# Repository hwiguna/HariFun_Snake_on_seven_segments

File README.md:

# HariFun_Snake_on_seven_segments

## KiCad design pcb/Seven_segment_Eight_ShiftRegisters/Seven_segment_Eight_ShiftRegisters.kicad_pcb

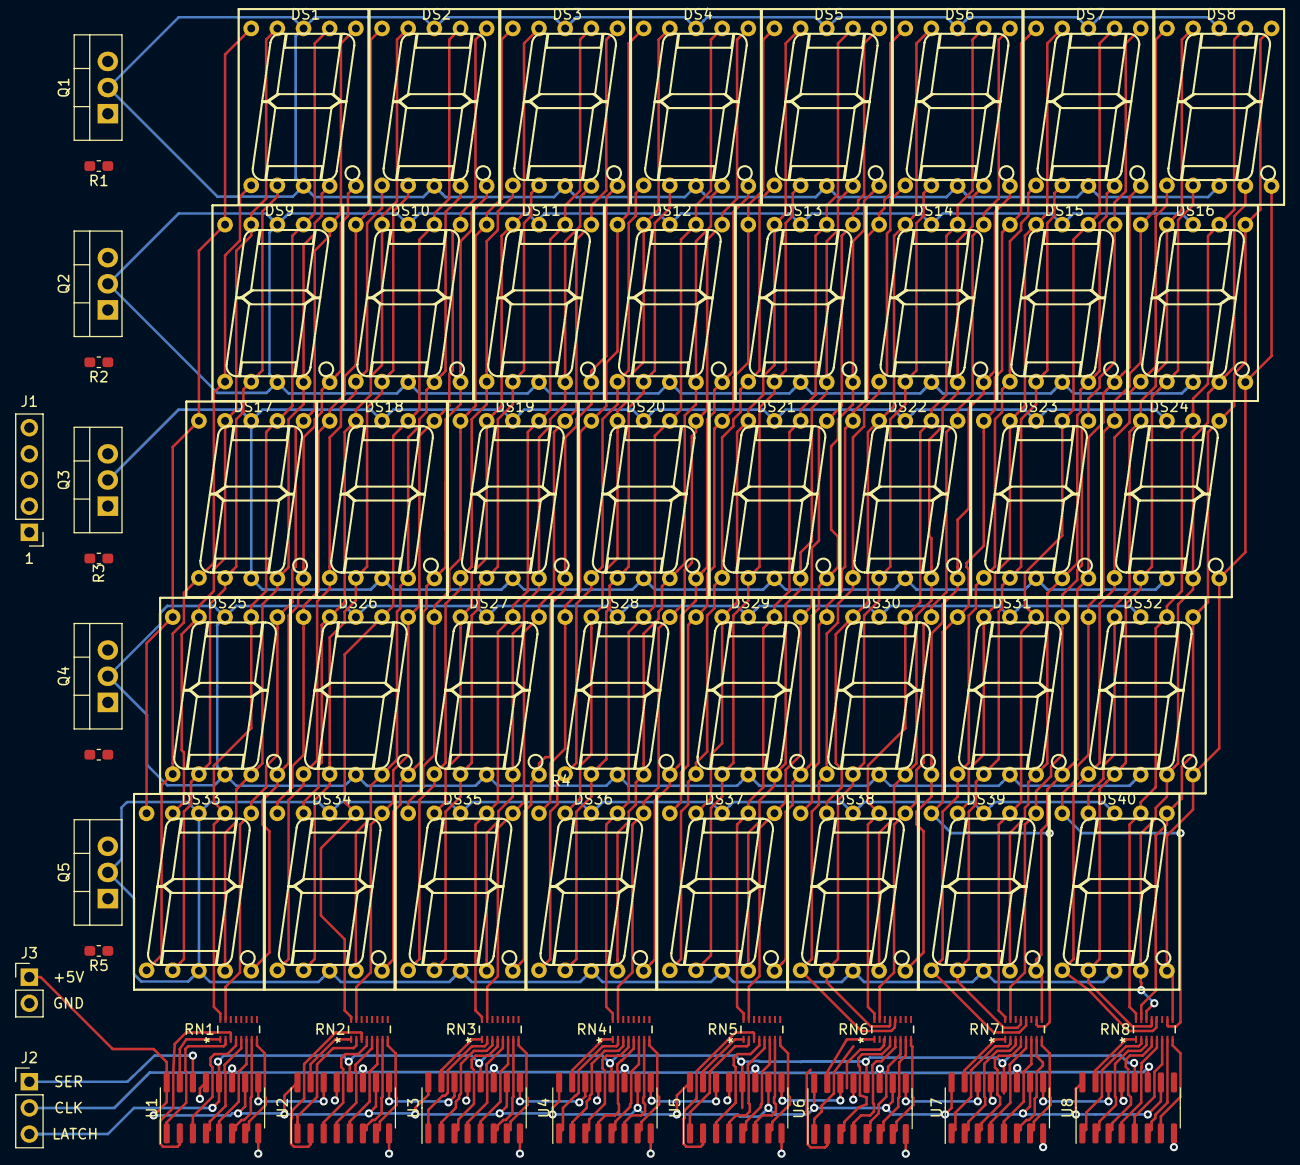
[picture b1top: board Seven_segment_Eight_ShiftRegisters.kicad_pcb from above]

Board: 2 copper layers, 69 parts (0 on the bottom side), 155 nets.

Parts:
DS1, DS2, DS3, DS4, DS5, DS6, DS7, DS8, DS9, DS10, DS11, DS12, DS13, DS14, DS15, DS16, DS17, DS18, DS19, DS20, DS21, DS22, DS23, DS24, DS25, DS26, DS27, DS28, DS29, DS30, DS31, DS32, DS33, DS34, DS35, DS36, DS37, DS38, DS39, DS40: 5161AS
J1: B5B-XH-A_LF__SN_; PinHeader_1x05_P2.54mm_Vertical
J2: B3B-PH-K-S_LF__SN_; PinHeader_1x03_P2.54mm_Vertical
J3: 22-23-2021; PinHeader_1x02_P2.54mm_Vertical
Q1, Q2, Q3, Q4, Q5: TIP120; TO-220-3_Vertical
R1, R2, R3, R4, R5: 1K; R_0603_1608Metric_Pad1.05x0.95mm_HandSolder
RN1, RN2, RN3, RN4, RN5, RN6, RN7, RN8: R_Pack08; EXB-2HV221JV
U1, U2, U3, U4, U5, U6, U7, U8: 74HC595; SOIC-16_3.9x9.9mm_P1.27mm

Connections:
+5V: J3.1, U1.10, U1.16, U2.10, U2.16, U3.10, U3.16, U4.10, U4.16, U5.10, U5.16, U6.10, U6.16, U7.10, U7.16, U8.10, U8.16
GND: J3.2, Q1.3, Q2.3, Q3.3, Q4.3, Q5.3, U1.8, U1.13, U2.8, U2.13, U3.8, U3.13, U4.8, U4.13, U5.8, U5.13, U6.8, U6.13, U7.8, U7.13, U8.8, U8.13
unnamed: DS1.1, DS9.1, DS17.1, DS25.1, DS33.1, RN1.12
unnamed: DS1.2, DS9.2, DS17.2, DS25.2, DS33.2, RN1.13
unnamed: DS1.3, DS1.8, DS2.3, DS2.8, DS3.3, DS3.8, DS4.3, DS4.8, DS5.3, DS5.8, DS6.3, DS6.8, DS7.3, DS7.8, DS8.3, DS8.8, Q1.2
unnamed: DS1.4, DS9.4, DS17.4, DS25.4, DS33.4, RN1.14
unnamed: DS1.5, DS9.5, DS17.5, DS25.5, DS33.5, RN1.9
unnamed: DS1.6, DS9.6, DS17.6, DS25.6, DS33.6, RN1.15
unnamed: DS1.7, DS9.7, DS17.7, DS25.7, DS33.7, RN1.16
unnamed: DS1.9, DS9.9, DS17.9, DS25.9, DS33.9, RN1.11
unnamed: DS1.10, DS9.10, DS17.10, DS25.10, DS33.10, RN1.10
unnamed: DS2.1, DS10.1, DS18.1, DS26.1, DS34.1, RN2.12
unnamed: DS2.2, DS10.2, DS18.2, DS26.2, DS34.2, RN2.13
unnamed: DS9.3, DS9.8, DS10.3, DS10.8, DS11.3, DS11.8, DS12.3, DS12.8, DS13.3, DS13.8, DS14.3, DS14.8, DS15.3, DS15.8, DS16.3, DS16.8, Q2.2
unnamed: DS2.4, DS10.4, DS18.4, DS26.4, DS34.4, RN2.14
unnamed: DS2.5, DS10.5, DS18.5, DS26.5, DS34.5, RN2.9
unnamed: DS2.6, DS10.6, DS18.6, DS26.6, DS34.6, RN2.15
unnamed: DS2.7, DS10.7, DS18.7, DS26.7, DS34.7, RN2.16
unnamed: DS2.9, DS10.9, DS18.9, DS26.9, DS34.9, RN2.11
unnamed: DS2.10, DS10.10, DS18.10, DS26.10, DS34.10, RN2.10
unnamed: DS3.1, DS11.1, DS19.1, DS27.1, DS35.1, RN3.12
unnamed: DS3.2, DS11.2, DS19.2, DS27.2, DS35.2, RN3.13
unnamed: DS3.4, DS11.4, DS19.4, DS27.4, DS35.4, RN3.14
unnamed: DS3.5, DS11.5, DS19.5, DS27.5, DS35.5, RN3.9
unnamed: DS3.6, DS11.6, DS19.6, DS27.6, DS35.6, RN3.15
unnamed: DS3.7, DS11.7, DS19.7, DS27.7, DS35.7, RN3.16
unnamed: DS3.9, DS11.9, DS19.9, DS27.9, DS35.9, RN3.11
unnamed: DS3.10, DS11.10, DS19.10, DS27.10, DS35.10, RN3.10
unnamed: DS4.1, DS12.1, DS20.1, DS28.1, DS36.1, RN4.12
unnamed: DS4.2, DS12.2, DS20.2, DS28.2, DS36.2, RN4.13
unnamed: DS4.4, DS12.4, DS20.4, DS28.4, DS36.4, RN4.14
unnamed: DS4.5, DS12.5, DS20.5, DS28.5, DS36.5, RN4.9
unnamed: DS4.6, DS12.6, DS20.6, DS28.6, DS36.6, RN4.15
unnamed: DS4.7, DS12.7, DS20.7, DS28.7, DS36.7, RN4.16
unnamed: DS4.9, DS12.9, DS20.9, DS28.9, DS36.9, RN4.11
unnamed: DS4.10, DS12.10, DS20.10, DS28.10, DS36.10, RN4.10
unnamed: DS5.1, DS13.1, DS21.1, DS29.1, DS37.1, RN5.12
unnamed: DS5.2, DS13.2, DS21.2, DS29.2, DS37.2, RN5.13
unnamed: DS5.4, DS13.4, DS21.4, DS29.4, DS37.4, RN5.14
unnamed: DS5.5, DS13.5, DS21.5, DS29.5, DS37.5, RN5.9
unnamed: DS5.6, DS13.6, DS21.6, DS29.6, DS37.6, RN5.15
unnamed: DS5.7, DS13.7, DS21.7, DS29.7, DS37.7, RN5.16
unnamed: DS5.9, DS13.9, DS21.9, DS29.9, DS37.9, RN5.11
unnamed: DS5.10, DS13.10, DS21.10, DS29.10, DS37.10, RN5.10
unnamed: DS6.1, DS14.1, DS22.1, DS30.1, DS38.1, RN6.12
unnamed: DS6.2, DS14.2, DS22.2, DS30.2, DS38.2, RN6.13
unnamed: DS6.4, DS14.4, DS22.4, DS30.4, DS38.4, RN6.14
unnamed: DS6.5, DS14.5, DS22.5, DS30.5, DS38.5, RN6.9
unnamed: DS6.6, DS14.6, DS22.6, DS30.6, DS38.6, RN6.15
unnamed: DS6.7, DS14.7, DS22.7, DS30.7, DS38.7, RN6.16
unnamed: DS6.9, DS14.9, DS22.9, DS30.9, DS38.9, RN6.11
unnamed: DS6.10, DS14.10, DS22.10, DS30.10, DS38.10, RN6.10
unnamed: DS7.1, DS15.1, DS23.1, DS31.1, DS39.1, RN7.12
unnamed: DS7.2, DS15.2, DS23.2, DS31.2, DS39.2, RN7.13
unnamed: DS7.4, DS15.4, DS23.4, DS31.4, DS39.4, RN7.14
unnamed: DS7.5, DS15.5, DS23.5, DS31.5, DS39.5, RN7.9
unnamed: DS7.6, DS15.6, DS23.6, DS31.6, DS39.6, RN7.15
unnamed: DS7.7, DS15.7, DS23.7, DS31.7, DS39.7, RN7.16
unnamed: DS7.9, DS15.9, DS23.9, DS31.9, DS39.9, RN7.11
unnamed: DS7.10, DS15.10, DS23.10, DS31.10, DS39.10, RN7.10
unnamed: DS8.1, DS16.1, DS24.1, DS32.1, DS40.1, RN8.12
unnamed: DS8.2, DS16.2, DS24.2, DS32.2, DS40.2, RN8.13
unnamed: DS8.4, DS16.4, DS24.4, DS32.4, DS40.4, RN8.14
unnamed: DS8.5, DS16.5, DS24.5, DS32.5, DS40.5, RN8.9
unnamed: DS8.6, DS16.6, DS24.6, DS32.6, DS40.6, RN8.15
unnamed: DS8.7, DS16.7, DS24.7, DS32.7, DS40.7, RN8.16
unnamed: DS8.9, DS16.9, DS24.9, DS32.9, DS40.9, RN8.11
unnamed: DS8.10, DS16.10, DS24.10, DS32.10, DS40.10, RN8.10
unnamed: DS17.3, DS17.8, DS18.3, DS18.8, DS19.3, DS19.8, DS20.3, DS20.8, DS21.3, DS21.8, DS22.3, DS22.8, DS23.3, DS23.8, DS24.3, DS24.8, Q3.2
unnamed: DS25.3, DS25.8, DS26.3, DS26.8, DS27.3, DS27.8, DS28.3, DS28.8, DS29.3, DS29.8, DS30.3, DS30.8, DS31.3, DS31.8, DS32.3, DS32.8, Q4.2
unnamed: DS33.3, DS33.8, DS34.3, DS34.8, DS35.3, DS35.8, DS36.3, DS36.8, DS37.3, DS37.8, DS38.3, DS38.8, DS39.3, DS39.8, DS40.3, DS40.8, Q5.2
unnamed: J1.1, R5.2
unnamed: J1.2, R4.2
unnamed: J1.3, R3.2
unnamed: J1.4, R2.2
unnamed: J1.5, R1.2
unnamed: J2.1, U1.14
unnamed: J2.2, U1.11, U2.11, U3.11, U4.11, U5.11, U6.11, U7.11, U8.11
unnamed: J2.3, U1.12, U2.12, U3.12, U4.12, U5.12, U6.12, U7.12, U8.12
unnamed: Q1.1, R1.1
unnamed: Q2.1, R2.1
unnamed: Q3.1, R3.1
unnamed: Q4.1, R4.1
unnamed: Q5.1, R5.1
unnamed: RN1.1, U1.15
unnamed: RN1.2, U1.1
unnamed: RN1.3, U1.2
unnamed: RN1.4, U1.3
unnamed: RN1.5, U1.4
unnamed: RN1.6, U1.5
unnamed: RN1.7, U1.6
unnamed: RN1.8, U1.7
unnamed: RN2.1, U2.15
unnamed: RN2.2, U2.1
unnamed: RN2.3, U2.2
unnamed: RN2.4, U2.3
unnamed: RN2.5, U2.4
unnamed: RN2.6, U2.5
unnamed: RN2.7, U2.6
unnamed: RN2.8, U2.7
unnamed: RN3.1, U3.15
unnamed: RN3.2, U3.1
unnamed: RN3.3, U3.2
unnamed: RN3.4, U3.3
unnamed: RN3.5, U3.4
unnamed: RN3.6, U3.5
unnamed: RN3.7, U3.6
unnamed: RN3.8, U3.7
unnamed: RN4.1, U4.15
unnamed: RN4.2, U4.1
unnamed: RN4.3, U4.2
unnamed: RN4.4, U4.3
unnamed: RN4.5, U4.4
unnamed: RN4.6, U4.5
unnamed: RN4.7, U4.6
unnamed: RN4.8, U4.7
unnamed: RN5.1, U5.15
unnamed: RN5.2, U5.1
unnamed: RN5.3, U5.2
unnamed: RN5.4, U5.3
unnamed: RN5.5, U5.4
unnamed: RN5.6, U5.5
unnamed: RN5.7, U5.6
unnamed: RN5.8, U5.7
unnamed: RN6.1, U6.15
unnamed: RN6.2, U6.1
unnamed: RN6.3, U6.2
unnamed: RN6.4, U6.3
unnamed: RN6.5, U6.4
unnamed: RN6.6, U6.5
unnamed: RN6.7, U6.6
unnamed: RN6.8, U6.7
unnamed: RN7.1, U7.15
unnamed: RN7.2, U7.1
unnamed: RN7.3, U7.2
unnamed: RN7.4, U7.3
unnamed: RN7.5, U7.4
unnamed: RN7.6, U7.5
unnamed: RN7.7, U7.6
unnamed: RN7.8, U7.7
unnamed: RN8.1, U8.15
unnamed: RN8.2, U8.1
unnamed: RN8.3, U8.2
unnamed: RN8.4, U8.3
unnamed: RN8.5, U8.4
unnamed: RN8.6, U8.5
unnamed: RN8.7, U8.6
unnamed: RN8.8, U8.7
unnamed: U1.9, U2.14
unnamed: U2.9, U3.14
unnamed: U3.9, U4.14
unnamed: U4.9, U5.14
unnamed: U5.9, U6.14
unnamed: U6.9, U7.14
unnamed: U7.9, U8.14

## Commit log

2019-08-03 Button works!
2019-08-03 We have tail
2019-08-04 Switched vector to define TIP of the snake head with direction behind it.
2019-08-04 Manual movement works.
2019-08-10 Starting PCB
2019-08-15 Playing with the oscilloscope
2019-08-26 Just checking in
2019-09-01 sync
2019-09-02 About to duplicate 3d models
2019-09-02 Displays are now 3D
2019-09-02 Redid pcb from scratch. Got ratsnest cleaned.
2019-09-02 About to try FreeRouting
2019-09-03 FreeRouting appears to be stuck routing so did it by hand afterall.

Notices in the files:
parts and their libraries:
Copyright 2016 Accelerated Designs. All rights reserved.
